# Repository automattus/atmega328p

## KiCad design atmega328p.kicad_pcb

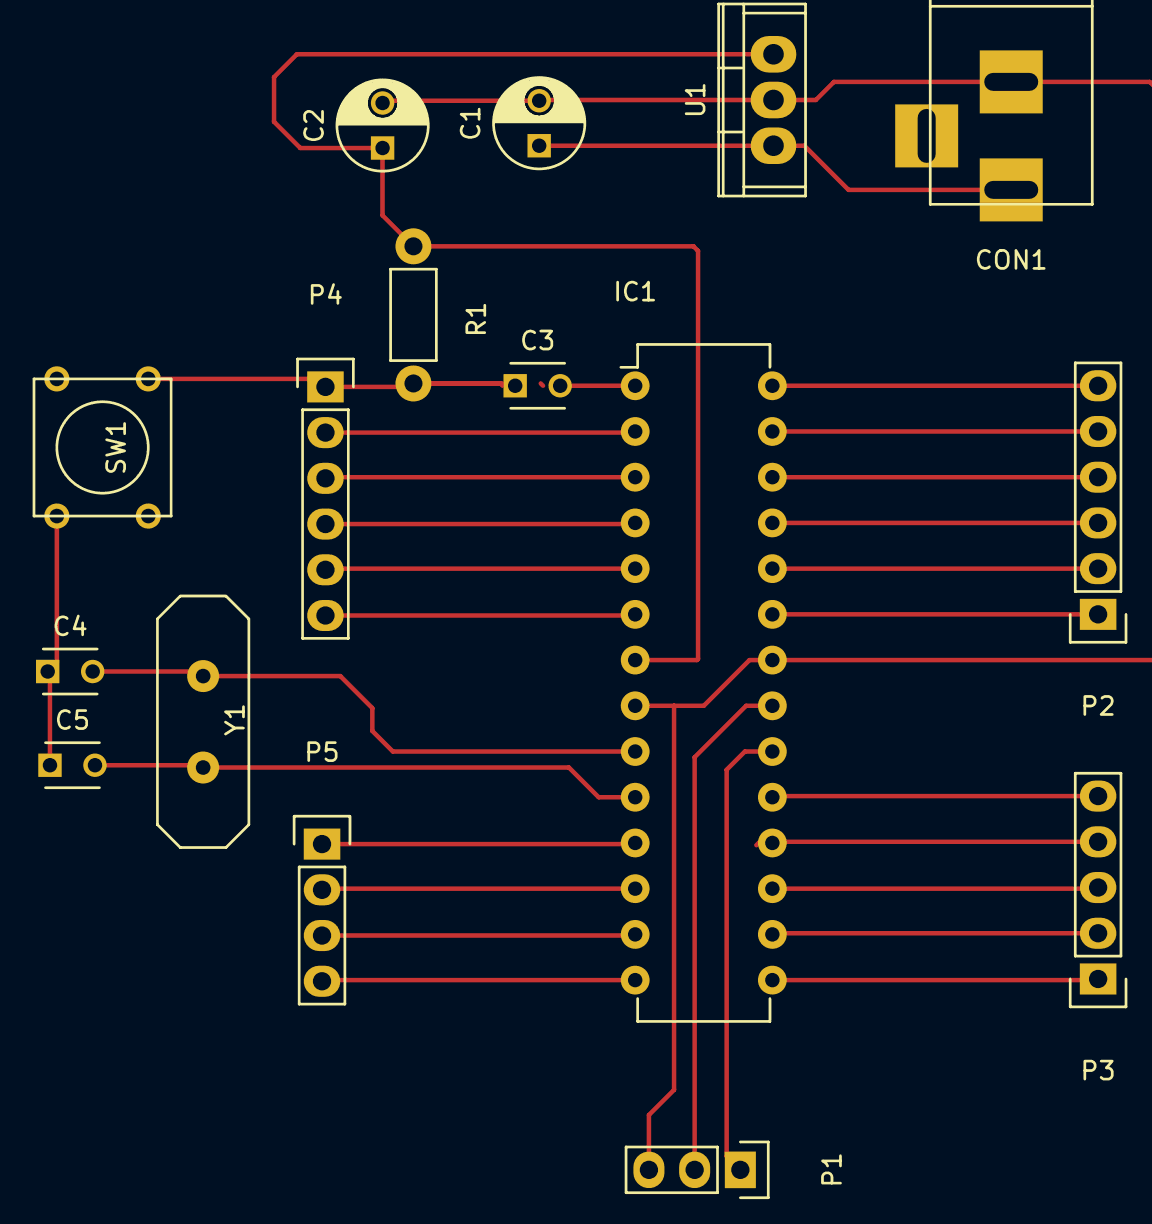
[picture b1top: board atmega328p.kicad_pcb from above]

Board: 2 copper layers, 16 parts (0 on the bottom side), 29 nets.

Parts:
C1, C2: CP1_Small; C_Radial_D5_L6_P2.5
C3, C4, C5: C_Small; C_Disc_D3_P2.5
CON1: BARREL_JACK
IC1: ATMEGA328P-P; DIP-28_W7.62mm
P1: CONN_01X03; Pin_Header_Straight_1x03
P2, P4: CONN_01X06; Pin_Header_Straight_1x06
P3: CONN_01X05; Pin_Header_Straight_1x05
P5: CONN_01X04; Pin_Header_Straight_1x04
R1: R; Resistor_Horizontal_RM7mm
SW1: SW_PUSH; SW_PUSH_SMALL
U1: LM7805CT; TO-220
Y1: Crystal_Small; HC-18UV

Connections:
/DTR: C3.1, P4.1, R1.2, SW1.1
/VCC: C2.1, IC1.7, R1.1, U1.3
/X1: C4.2, IC1.9, Y1.1
/X2: C5.2, IC1.10, Y1.2
unnamed: C1.1, CON1.1, U1.1
unnamed: C1.2, C2.2, CON1.2, IC1.8, IC1.22, P1.3, U1.2
unnamed: C3.2, IC1.1
unnamed: IC1.2, P4.2
unnamed: IC1.3, P4.3
unnamed: IC1.4, P4.4
unnamed: IC1.5, P4.5
unnamed: IC1.6, P4.6
unnamed: IC1.11, P5.1
unnamed: IC1.12, P5.2
unnamed: IC1.13, P5.3
unnamed: IC1.14, P5.4
unnamed: IC1.15, P3.1
unnamed: IC1.16, P3.2
unnamed: IC1.17, P3.3
unnamed: IC1.18, P3.4
unnamed: IC1.19, P3.5
unnamed: IC1.20, P1.1
unnamed: IC1.21, P1.2
unnamed: IC1.23, P2.1
unnamed: IC1.24, P2.2
unnamed: IC1.25, P2.3
unnamed: IC1.26, P2.4
unnamed: IC1.27, P2.5
unnamed: IC1.28, P2.6

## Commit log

2016-04-18 :tada: Added .gitattributes & .gitignore files
2016-04-18 teste
